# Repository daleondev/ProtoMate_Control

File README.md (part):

# ProtoMate Control

Control software running on the robot controller of the ProtoMate SCARA Robot.

## Current target: Arduino GIGA R1 WiFi

**M4 runs `io::Application`; M7 runs `ui::Application`.** Each independently
linked image owns its main, ThreadX kernel, C++ runtime, heap, TLS, threads,
message bus, coroutine context and ICC bridge. Common implementations are
compiled separately for each core. ICC uses bounded shared-SRAM queues with
urgent, normal and background lanes; M7 writes the physical USB-C CDC console.

The STM32H747 CubeMX, HAL, external-flash bootstrap and build port are implemented.
**Both applications boot from QSPI; USB/ICC services and STEP generation under combined load are verified.**
Factory backups are preserved. [Wiring, memory, backup/flash/debug commands and acceptance gates](#arduino-giga-hardware-boot-and-bring-up)
are documented below. Linux keeps the paired in-process transport for tests.

M4 exposes STEP/DIR/enable, switches, DM542T/TMC2209 drivers, feedback and the
future EtherCAT SPI connection. M7 owns the RGB LED, user button, display/touch
and console. M7 mounts persistent internal-flash storage at `/flash`; M4 does
not mount the volume. Both runtimes include filesystem support.
Motor construction leaves all drivers disabled; initialization, enabling and
motion are explicit CLI operations. Display/touch bring-up uses `display`
commands. The shared TouchGFX robot HMI opens Home on M7 and Linux, using the same
motion client and job history as the CLI. See the [HMI guide](docs/gui/hmi/README.md).

## Remote-control integration and future supervision

OPC UA is integrated as a third UI frontend alongside GUI and CLI. The LAN9255
supervisor remains future work. This hobby project makes no certification or
SIL/PL claims. Powered robot commissioning remains separate from software and
motor-disconnected electrical tests.

### OPC UA interface on M7 using open62541

**Remote-motion endurance is not yet qualified:** intermittent network/server latency
can exceed the unchanged 500 ms control-source deadline. Read-only monitoring and
short electrical workflows pass; normal firmware starts with remote permission OFF.
See the measured blocker in the qualification report linked below.

The server uses the existing motion client, planner, source-aware execution jobs
and M4 admission. Its explicit reflection catalog publishes 187 application nodes
(68 methods), with stable string NodeIds and bounded typed records. The namespace
is `urn:protomate:control`; default subscriptions publish at 100 ms (50 ms minimum).
No network read requests fresh IO work.

- `src/ui/opcua` (`proto::ui::opcua`) owns the catalog, server, NetX/POSIX ports and
  allocator. `platform/network` owns Wi-Fi/SDIO/NetX. M4 links neither stack.
- GUI and OPC UA share `ui::Services`; CLI retains the same application-owned
  motion client and job history. Existing ownership, units, planning and stop
  semantics apply to all frontends.
- Remote commands require local permission, **OFF on every boot**. Anonymous
  SecurityPolicy None is intended for the trusted LAN. The client worker checks
  500 ms remote expiry independently of networking/rendering, using 100 ms
  heartbeats and explicit held-jog supervision. Disconnect never replays motion.
- Settings → Network and USB `network setup` provide local setup. One Wi-Fi
  profile is saved on internal flash; passwords are not exposed remotely or logged.
  Linux uses OS networking. `opcua status|start|stop|restart` and
  `opcua remote on|off` expose local management.
- Dedicated SDRAM reservations provide 512 KiB for OPC UA, 256 KiB for networking
  and 128 KiB for presentation snapshots/USB byte rings, preserving active
  framebuffers, M4 memory and ICC SRAM4. Another 128 KiB remains unassigned.
  The server's internal stack is 14 KiB, based on measured complete-catalog use.

See the [integration guide](docs/opcua/README.md),
[generated node reference](docs/opcua/nodes.md),
[architecture and memory diagrams](docs/opcua/architecture.md), and
[measured qualification status](docs/opcua/verification.md).
The [standalone Wi-Fi sample](examples/opcua_sample/README.md) remains buildable.

### LAN9255 SAM E53 supervisor with FSoE

Explore using the integrated SAM E53 as a dedicated supervisor and EtherCAT
gateway, including an FSoE endpoint for a remote FSoE controller. This would
replace the erased-SAM/direct-GIGA-to-ESC arrangement for this future variant:

```text
EtherCAT + FSoE -> LAN9255 ESC -> SAM E53 -> separate SPI -> GIGA M4
                                  |
                                  +-> independent motor shutdown hardware
```

- Restore SAM firmware and move EtherCAT slave application ownership there.
  Process FSoE locally; forward ordinary command/status data to M4 through a
  bounded SPI protocol. FSoE requires a corresponding remote FSoE main instance;
  an ordinary EtherCAT master alone does not supply that logic.
- Investigate the separate SPI exposed at mikroBUS J18 for the GIGA link.
  J3 taps the ESC bus and must not be driven by two independent masters. The
  current documented J3 wiring stays unchanged until this variant is implemented.
- Give the supervisor physical authority to withdraw motion permission without
  GIGA cooperation. A GIGA enable request may only enable motion while the
  supervisor, watchdog and local protective inputs also permit it.
- Default to inhibited operation during reset, power loss or watchdog expiry;
  latch trips and require deliberate recovery. Include an external watchdog
  driven by completed supervision cycles, not an autonomous timer heartbeat.
- Evaluate independent driver-enable inhibition and monitored switching of the
  motor-power branch while keeping controller power available. Select the output
  topology after checking failure behavior, stored energy and regeneration.
  DM542T/TMC2209 enable inputs are ordinary controls, not documented STO inputs;
  account for the existing interface polarity rather than simply disconnecting
  an enable wire. A stop message to M4 alone cannot provide this authority.
- Determine whether Axis 3 needs a brake or other load-retention mechanism before
  removing holding torque. Controlled deceleration through M4 is useful, but
  independent shutdown must still work if M4 fails.
- Verify with motors disconnected first: GIGA/SAM stalls and resets, lost/stale
  FSoE and SPI traffic, broken supervision, shutdown-output faults and prevention
  of unintended restart. Later validate actual stopping and load retention.

FSoE protects communication integrity; it does not by itself make the SAM,
outputs or mechanics fault tolerant. The intended outcome is a tested hobby
supervisor with independent shutdown, without a certification program.
References: [EVB schematic, page 22](docs/ethercat/EVB-LAN9255-Evaluation-Board-Users-Guide-50003106.pdf)
and [ETG FSoE overview](https://www.ethercat.org/safety/).

## Motion API: motors, axes and robot

M7 owns the motion client, bounded job history, axis conversion and robot planning.
M4 owns admission, driver state, execution and local stopping. CLI commands are
asynchronous: a returned job ID means submitted; `motion jobs <id>` reports IO
acceptance and the eventual result. Returning to the prompt does not cancel a move.

| Control | Units | Commands |
|---|---|---|
| `motor` | Shaft degrees / rpm | Existing raw moves, homing, dynamics and buffering |
| `axis` | Axis 1/2 degrees; Axis 3 mm | `status`, `move`, `moveto`, `home`, `jog`, `stop` |
| `robot` | Joint coordinates or Cartesian mm | `status`, `home`, `move joints`, `moveto joints`, `move point`, `moveto point`, `stop` |
| `motion` | Shared lifecycle/jobs | `init`, `enable`, `disable`, `status`, `jobs`, `wait`, `cancel`, `stop`, `abort` |

`motion init` leaves drivers disabled. Initialize and enable explicitly, then home
before absolute/axis/robot motion. Execution requires the native simulator's
mechanical configuration or a verified physical configuration. The physical
configuration is deliberately unset. Preview fixtures are never substituted for it.

Examples after homing:

```text
axis move shoulder -5 --speed 10
axis jog z -1 --duration 1
robot moveto joints 30 -30 10 --speed 0.25
robot move point -1 -1 0
motion jobs
motion wait 4 --timeout 10
motion cancel 4
```

Axis dynamics are deg/s, deg/s², deg/s³ or mm/s, mm/s², mm/s³. Zero/omitted values
select configured defaults. Robot `--speed`, `--accel`, `--decel` and `--jerk` are
factors of configured limits in (0,1]; zero selects defaults. Speed defaults to
0.25. Cartesian point moves interpolate **joints**, so their TCP paths can curve.
Straight Cartesian paths remain previews; blending, live override and hold/resume
are not exposed as executable robot features.

M4 atomically excludes command families. Raw motor commands can coexist under
existing per-motor buffering rules; axis jobs may run on separate axes; a robot
job reserves all three. Families cannot mix. Reservations start before executable
planning and last through deceleration and cleanup. Busy results identify the
owner. Configuration/state revisions are checked again before starting; stale
plans emit no pulses. Read-only status and previews remain available.

`motion jobs` retains 32 execution records. Waiting explicitly does not transfer
ownership; a wait timeout leaves the motion running. `axis stop` also stops the
whole group if that axis belongs to a robot job. Axis/robot stops decelerate with
holding torque retained. Raw `motor stop` remains an immediate abort; abort and
disable invalidate affected references. No stop or reconnect resumes motion.

The configured ceiling is **6,250 pulses/s on each axis**, with microsteps
**16 / 16 / 8**. Joint/point moves share one normalized profile and one scaled
stopping-progress profile. Endpoints are quantized once, and completely zero
moves do not arm outputs. Finite programs, including stopping continuations, are
limited to **90 seconds**. Continuous jog uses rolling timing toward the actual
soft-limit boundary; the default timed jog requests deceleration after one second.

Two deadlines serve different purposes: the UI ownership lease is **250 ms**,
renewed in one batch every **50 ms**; local M4 execution maintenance uses a
**40 ms** renewal and **80 ms** committed frontier. The execution worker still
services refills and stops every millisecond; its local keepalive remains 40 ms.
UI loss selects an already
installed brake on M4. An M4 execution failure invokes the hardware guard and
invalidates uncertain references; it is not a guaranteed controlled stop.

The Linux workflow exercises the native simulated plant through the production
CLI, ICC and controller. Brake construction preserves the incoming state and
accepts only binary64 roundoff at acceleration limits (eight machine epsilons,
relative to the limit). Exact captured-input, phase-boundary, scaling and
out-of-limit regressions cover this numerical boundary.

The current motion review has separate software and electrical results. Short
motor-disconnected analyzer captures pass for raw commands (**18/18/9 pulses**),
coordinated completion (**400 per axis**) and controlled stopping (**266 per axis**).
HIGH time is 120–121 samples at 24 MHz; coordinated rising-edge skew is at most
one sample. Physical ENABLE remains inactive throughout. These captures peak
near 711 pulses/s and do **not** qualify the configured 6,250-pulse/s ceiling.

The concurrent jog/independent-axis ICC failure is fixed. The M4 urgent sender
was exhausting the heap when allocating a 4,228-byte temporary coroutine for
another outgoing frame; UI then reported the missing heartbeat. Each sender now
reuses one persistent frame allocated at startup. A host allocation regression
and repeated application-level overlaps verify the fix. Heartbeat, ownership
and motion deadlines are unchanged. See the [current review](docs/motion-current-state/review.md)
for firmware identities, capture results and the remaining physical qualification.

The review fixes an overall homing deadline, missing preparation-version
validation, an interrupted-wait wakeup race, telemetry waiting on raw startup's
command lock, a native display-mutex preemption deadlock, and an unnecessary
peak allocation when STEP scratch storage grows. Preparation/start failures now
retain their stage and allocation failures report capacity exhaustion. The
native simulator caches mechanical configuration before starting live transport.
Its clock waits for interrupt-woken controller work to suspend before advancing
the next event, and simulated display refresh uses that same clock. This prevents
instrumentation overhead from starving homing behind repeated periodic wakeups.

The ordinary interaction objective remains approximately **200 ms to start
changing motion**, not to reach rest. The current captures establish pulse
behavior, not a worst-case admission/stop-onset bound or maximum-rate endurance.
The complete native motion workflows pass with ASan/UBSan, including
homing → stop → homing and checks for unwanted seek pulses after switch contact.
This functional simulation does not qualify hardware scheduling or timing.
Clang-tidy is clean across all 430 production compilation contexts (Linux, M4
and M7), with no parse blockers; unit tests remain excluded.
See the [current review](docs/motion-current-state/review.md) for exact
build, test, firmware and capture evidence.

Powered mechanical acceptance requires calibrated limits and transmissions.
[Executor architecture and verification](src/io/motion/EXECUTOR.md).

## Native Linux robot simulation

Build as usual, then launch **`build/debug-linux/Application`**. This one
executable forks into a native simulation process and a controller process,
opening the TouchGFX window plus a separate robot window. Use
`--headless` to omit only the robot window. See [simulator usage and model
boundaries](src/simulation/README.md) for the provisional physical profile,
fault controls, persistent media, signal capture and verification commands.

The robot window displays native simulated shaft/axis state, not motion requests
or controller position estimates. The controller retains the production IO
state machines, drivers, STEP generator, FileX/LevelX and UI/IO ICC. Emulated
motion hardware and physical state live in the separate native process.

## Platform layout

| Directory | Responsibility |
| --- | --- |
| `platform/boot/` | Board startup, recovery images, memory protection and GIGA flash partition layout |
| `platform/hal/` | Hardware contracts, drivers, devices, board wiring and core selection; includes the inter-core lane contract |
| `platform/simulation/` | Linux simulator wire contract, shared memory, HAL mailbox and interrupt handoff |
| `platform/runtime/` | ThreadX integration, C/C++ runtime and filesystem/storage implementations |

The GIGA partition header is shared by boot MPU setup and the runtime flash
adapter; the partition addresses and erase geometry are defined in one place.

## Application layout

| Directory | Responsibility |
| --- | --- |
| `src/common/` | Shared contracts, motion profiles, application lifecycle concept, ICC bridge and transports |
| `src/io/` | M4 entry point, IO application, motor ownership and motion execution |
| `src/simulation/` | Native hardware process, machine models, independent SDL/OpenGL viewer and tests |
| `src/ui/` | M7 entry point, UI application, CLI, shared GUI, axis conversion and robot planning |

Each firmware compiles only its own application target, `proto::io` or
`proto::ui`. Both use `proto::common`. These are compiled static libraries;
their nested `INTERFACE` targets collect sources privately into the owning
library. Tests and examples link the compiled libraries so implementation files
are compiled once per build. Public include paths start at `src/`, for example
`common/icc/bridge/Bridge.hpp` and `io/app/Application.hpp`. The Linux entry point in
`src/main.cpp` retains the in-process paired transport for host development and
lifecycle tests. It is not compiled into either GIGA image.

The [application concept](src/common/app/Application.hpp) enforces `void start()`,
`void requestStop()` and `void join()` without inheritance. Construction initializes
logging; application workers launch in `start()`. `start()` is one-shot;
`requestStop()` is an idempotent thread-safe notification; `join()` waits for
completion. Destruction requests a stop and joins. Call start/join/destruction
from the lifecycle owner, outside workers.

`runtime::thread::Definition` annotations in each `app/Application.hpp` declare
its threads; `app/Application.cpp` defines their entries.
[ThreadGroup](platform/runtime/ThreadGroup.hpp) creates all workers before
releasing them. The ICC worker runs the context; the application worker waits
for a stop request, then drains the bridge before stopping its context. Peer
shutdown or link failure wakes the application worker. Each application requires
a transport; the bridge is a concrete member with no optional execution path.

Each application exposes a lifecycle `state()`: `Starting`, `Ready`, `Stopping`,
`Stopped` or `Fault` ([shared definition](src/common/app/State.hpp)). IO publishes
its state on the latest-only `io/controller/state` topic every 100 ms. UI owns
[`SystemState`](src/ui/app/SystemState.hpp), combining its local state, the
received IO state and ICC connection health; `ui::Application::systemState()`
returns this snapshot. Refresh uses timers on the existing ICC workers.
The CLI command `state` displays the same combined state and LED colour, both
controller states, and whether the received IO state is fresh. `help state`
describes the command; reading state does not issue an IO request or move motors.

UI displays the combined state on the GIGA's onboard RGB LED:

| Colour | Meaning |
| --- | --- |
| Green | Both applications are `Ready`, ICC is connected and IO state is fresh |
| Yellow (red + green) | Starting, awaiting IO state, or orderly stopping/stopped |
| Red | Application fault, ICC failure, or no IO state for 500 ms while connected |

Blue stays off. Freshness uses UI's receive clock; timestamps need not be
synchronized between cores. Fault indications latch until application restart;
shutdown cannot clear them. Final topic delivery is best effort, with ICC's
orderly goodbye distinguishing normal peer shutdown from communication failure.
These are **controller application states**, not motor readiness or enable
indicators. Green does not mean drivers are initialized, motors are referenced,
or motion is enabled. Motor telemetry and admission checks remain separate;
an LED or lost communication cannot confirm that physical motion has stopped.
GIGA Debug verification checks the LED GPIO levels: green during normal paired
operation, yellow after CLI shutdown, and red after halting M4 until a coordinated
restart. Shared motor enable remains inactive throughout these checks.

[`io::motion::Controller`](src/io/motion/Controller.hpp) owns three `StepperMotor`
instances, their shared STEP generator and enable output. Drivers and feedback
belong to each motor. `initializeDrivers()` configures the drivers and starts the
idle timebase; `enable()` verifies readiness before energizing the motors.
Controller move/reference methods preserve independent axis execution and
buffering. `stop(id)` stops one motor, `stop()` stops all while retaining torque,
and `disable()` also removes enable and invalidates references. Driver faults
immediately drop shared enable; a diagnostic worker cancels and joins all motion.
Recovery requires explicit initialization and enabling. IO shutdown disables the
motors before draining ICC. Motor settings live in `io/app/Application.cpp`:
1.8° full steps, 16/16/8 microsteps for M1/M2/M3 and placeholder 135° shaft
reference coordinates. These shaft placeholders do not supply a calibrated axis
or robot configuration.

The motor service dispatcher handles urgent stop/disable requests and telemetry.
One bounded command worker (priority 2, 16 KiB ARM stack) executes ordinary services and program preparation;
additional ordinary requests return `Busy` while it is occupied. UART verification
and initialization run outside the controller admission lock, and enable settling
is cancellable. Stop invalidates pending initialization/enable work and queued
ordinary requests; only a new explicit command can enable the motors afterwards.
Velocity updates enqueue under the admission lock and wait outside it.

`src/ui/cli/` contains the annotation-based parser, filesystem and utility
commands, Linux terminal frontend and direct motor commands. Registration uses
`ui::cli::register_commands` with a parser owned by the CLI thread. Each command
module has its own per-parser `std::call_once` guard. Motor callbacks use the
application-owned `ui::motion::Client`; only IO owns the physical controller.

M7 exposes the CLI through **USB-C CDC** (no UART bridge). Use `help` or
`help <command>`. Available commands are `pwd`, `cd`, `ls`, `touch`, `mkdir`,
`rmdir`, `rm`, `cp`, `mv`, `cat`, `echo`, `grep`, `time`, `stack`, `heap`, `state`,
`display`, `motor`, `motion`, `axis` and `robot`.
Quoting, wildcard expansion, pipes and `>`/`>>` redirection are supported.
For example, `echo "hello world" | grep world` and `time "heap io"`.
`heap ui` / `stack ui` inspect UI locally; `heap io` / `stack io` request IO's
memory diagnostics through the `io/memory` ICC service. The controller argument
is required. `time` measures execution on UI, including any remote round-trip wait.
Filesystem commands use the host filesystem on Linux and FileX on M7.
On GIGA, `/flash` is persistent internal-flash storage; see
[persistent files](#persistent-files-in-internal-flash) for capacity and behavior.

Motor commands use **motor-shaft degrees and rpm for all three motors**, including
M3. `motor` prints a guide; `help motor move` lists annotated options.

```text
motor driver init
motor enable
motor move m1 -90 --speed 5
motor jobs
motor status m1
motor stop m1
motor disable
```

- `motor status [m1|m2|m3|all]` shows commanded position/velocity, feedback and reference state.
- `motor driver status [motor|all]` shows driver readiness, alarms and latched faults.
- `motor driver init` initializes/recover drivers and the STEP timebase while disabled.
- `motor enable` / `motor disable` operate the shared enable; disabling stops work and invalidates references.
- `motor move <motor> <degrees> --speed <rpm>` submits a relative move.
- `motor moveto <motor> <degrees> --speed <rpm>` requires successful homing.
- `motor home <motor> [--seek 5] [--latch 0.5] [--timeout 30]` seeks, releases, slowly re-latches and finally releases the switch again, retaining the coordinate established at the latch.
- `motor speed <motor> <rpm>` replans the uncommitted remainder of an active move. It can be rejected once all remaining pulses are already scheduled.
- `motor defaults <motor> [--accel <deg/s²>] [--decel <deg/s²>] [--jerk <deg/s³>]` reads/updates idle motor defaults in RAM.
- `motor stop [motor|all]` aborts the selected motor and its buffered successor while retaining holding torque and invalidating its reference. Other independent motors continue; targeting a current robot group aborts that whole group.
- `motor jobs [id]` uses the shared execution-job registry. `motion jobs [id]` shows all command families; returning from a CLI command does not cancel its job.

Moves accept `--accel`, `--decel`, `--jerk` (zero selects the motor default),
`--timeout` (seconds, zero means unlimited) and `--buffer` (`aborting`, `buffered`,
`blending-low`, `blending-previous`, `blending-next`, `blending-high`). A motor can
have one queued successor. A configured default jerk of zero selects a trapezoid.
`accepted` includes queued/executing work; only a terminal result confirms its outcome.
INDEX feedback is labelled as a pseudo measurement of driver phase.
Axis conversion and coordinated positioning are exposed through `axis` and `robot`,
with the family exclusion and configuration requirements described above.

Linux uses ncursesw with separate logs, line editing and command history when
attached to a terminal. Redirected input/output, `TERM=dumb`, or
`SIMPLCITY_CLI_PLAIN=1` select the plain frontend. Console EOF, Ctrl-C, or Ctrl-D
on an empty interactive line shuts down the application pair. Application or
peer shutdown also interrupts an idle CLI. Plain/serial lines are limited to
4096 bytes; oversized lines are rejected. M7 receives bytes into a bounded IRQ
buffer while commands execute; input errors stop the console instead of
executing truncated input. The serial frontend echoes input, so disable local
echo in the PC terminal.

The shared message catalogs live in `src/common/icc/catalog/`:

- [topics.hpp](src/common/icc/catalog/topics.hpp): `Topics`, with `TopicPublisher` annotations.
- [services.hpp](src/common/icc/catalog/services.hpp): `Services`, with `ServiceProvider` annotations.
- [actions.hpp](src/common/icc/catalog/actions.hpp): `Actions`, with `ActionProvider` annotations.

Both applications register all three catalogs in their constructors using their
own IO/UI role. `Topics::io_logs` carries IO log text to UI. `Topics::io_motor_state`
publishes all three motor states at up to 20 Hz, including while idle or disabled.
Both the bridge and UI subscription use latest-only delivery. `Services::io_memory`
provides memory diagnostics. `Services::io_motor` carries initialization,
enable, speed and default-setting requests. `Services::io_motor_stop` reserves
urgent transport capacity for stop/disable. `Actions::io_motor_motion` carries
raw individual moves and homing, with periodic feedback and terminal results.
`Services::io_trajectory` handles authoritative snapshots, reservations and bounded
program preparation. `Services::io_trajectory_control` uses the urgent lane for
batched lease renewal, stop, abort and reservation release. `Actions::io_motion`
starts a prepared axis/robot program and retains its lifecycle through cleanup.
Shared motor payloads live in `src/common/motion/Motor.hpp`; compact versioned
program packets live in `src/common/motion/Trajectory.hpp`. Both use the existing
ICC bridge rather than a separate motion transport.

`motor status` and `motor driver status` read UI's latest snapshot without a
service request. Missing telemetry, disconnection and samples older than 500 ms
produce explicit errors. Freshness uses UI's local receive clock; the snapshot's
IO timestamp is informational, and its increasing sequence rejects duplicate or
out-of-order samples. The worker waits 50 ms after publishing; blocking IO or ICC
processing can extend the interval. It does not catch up missed publications in
a tight loop that would starve diagnostics and logging. Command replies contain the outcome, `commandGeneration`
and operation-specific values (motion defaults or the scheduled speed-change
pulse), without copying motor states. Actions still report acceptance and terminal
results independently of telemetry.

IO's application worker drives `io::motion::Server`; blocking driver operations
and joins stay outside the ICC context. Controller completion callbacks only
wake this worker. UI's application worker caches telemetry and dispatches action callbacks for
`ui::motion::Client`, retaining its job handles until completion. Services and
action admission time out after three seconds; execution uses the requested
motion timeout. Lease renewals have a shorter 150 ms service timeout and only
one renewal request may be outstanding. No request is automatically retried. `commandGeneration`
rejects submissions overtaken by a stop, disable or initialization. Acknowledgements
update UI's generation immediately, so subsequent moves do not wait for telemetry;
older snapshots cannot roll it back. IO validates admission against its current
state rather than trusting UI's cache. Link shutdown
drains IO motion and disables the shared enable before closing its bridge. UI
reports uncertain communication outcomes as unknown rather than claiming a stop.

Diagnostic snapshots and collection live in `src/common/diagnostics/`. IO's
`io::diagnostics::Server` collects them on a dedicated worker; the CLI formats
both local and remote results using the same tables. Remote requests have a
two-second timeout, participate in UI shutdown cancellation and never fall back
to UI measurements on failure. At most two requests are outstanding at the IO
provider. Each response fits one ICC frame and includes up to 32 thread records
with names limited to 31 characters; omitted threads and shortened names are
identified in the output. Stack usage is sampled/saved usage and a recorded
high-water mark, not a continuous measurement. The collection copies thread
records under the local ThreadX interrupt lock, without allocation or formatting.
On Linux both controllers share the process allocator and ThreadX kernel; the
output explicitly labels that scope even when the request travels through ICC.

`reset all` immediately aborts motion and resets the complete GIGA, including both
controllers. STEP/enable outputs are inhibited before reset; startup leaves motors
disabled and references must be established again. During reset itself, GPIOs are
inputs: external STEP pull-downs and the disable-state enable bias remain required.
USB CDC disconnects during
reboot. This is **not** a controlled stop: use `motion stop` first when deceleration
is required. Individual `reset ui` / `reset io` requests are rejected without any
reset. ST does not guarantee CPU-only watchdog reset (RM0399 §9.7.36), and our ICC
transport currently requires coordinated startup. Linux reports hardware reset as
unsupported; close and restart the simulation instead.

IO's Pneumo sink publishes already formatted records on `io/logs`; UI adds an
`[IO]` prefix and writes them directly to the console without logging them again.
Original timestamps and levels remain intact. Each record is limited to 384 bytes
(longer records end with `[truncated]`), and both the outgoing bridge subscription
and UI subscriber retain the newest 16 records. Overflow counters are available
through bridge/subscriber statistics; the sink separately counts truncations.
Console output runs on a notification-driven UI worker, never in ICC callbacks.
On Linux it uses the console broker, including buffering before ncurses starts.

UI installs its own Pneumo sink for all levels before its first startup log.
It prefixes local records with `[UI]` and calls `cli::writeLog`, the same output
function used by the IO subscriber. Received IO records retain `[IO]` and bypass
the local sink. The CLI frontend does not replace either logging route.

The M4 entrypoint installs this sink as Pneumo's default for all levels. The motion
controller also passes it explicitly to its motors, so Linux's IO logs use the same
ICC path while UI retains its separate console routing in the shared process.
Shutdown closes the IO sink before stopping ICC and wakes/joins UI's log worker.
Logs are best effort and may be discarded at shutdown. These bounds apply to the
ICC path; Pneumo's existing asynchronous logger queue is separate. Logging remains
a thread-context operation, not an ISR-safe or allocation-free API.

| Thread in each GIGA image | ThreadX priority (lower is higher) | Stack |
| --- | --- | --- |
| ThreadX timer worker | 0 | Port default |
| `io.iccThread` | 4 | 20 KiB (32 KiB on Linux) |
| `intercore.notify` | 3 | 2 KiB (8 KiB on Linux) |
| `ui.iccThread` | 4 | 32 KiB |
| `ui.cliThread` | 5 | 16 KiB (64 KiB on Linux) |
| M4 motion executor | 1 | 8 KiB (16 KiB on Linux) |
| M4 command/preparation worker | 2 | 28 KiB (24 KiB on Linux) |
| M4 raw motion/homing worker (up to three) | 16 | 10 KiB (16 KiB on Linux) |
| `io.applicationThread` | 3 | 16 KiB |
| `ui.applicationThread` | 6 | 16 KiB |
| Runtime main/application entry | 15 | 8 KiB |
| M4 motion diagnostics | 18 | 6 KiB (8 KiB on Linux) |
| `io.diagnosticThread` (heap/stack service) | 20 | 4 KiB (16 KiB on Linux) |
| `ui.logThread` | 20 | 8 KiB |
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
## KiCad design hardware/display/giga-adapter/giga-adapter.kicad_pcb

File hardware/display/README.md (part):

# Smartwin–GIGA display adapters

**Local electrical, manufacturing and recorded visual checks pass.**
Both use complete outer-layer routing, two continuous inner GND planes and
stitched outer fills. Authorized placement changes put GIGA R33–R48 beside J8
and reposition display C9/TP8 and R16/R17 for direct supply and supervisor connections.
Connector positions and board mechanics remain fixed.
See [current validation status](manufacturing/layout-unification-status.json).
The matching releases below are ready for upload and AISLER processing review.

**Component selection:** the working KiCad schematics and PCBs now contain the
approved [purchasing selections](procurement/README.md), including their actual
manufacturer, MPN and voltage ratings. This is a component-metadata update;
copper, footprints, placement and silkscreen are unchanged. The frozen release
archives below retain their original component metadata. Use the working projects
and current procurement list for assembly; this update does not constitute a new
fabrication release or renew the archives' source-hash inspection records.

The **four-layer display adapter (revision G)** and **four-layer GIGA adapter
(revision F)** connect the Smartwin **SMMH0701024600S-C20** to the Arduino
**GIGA R1 WiFi**, preserving the firmware's display pin assignments.
Open either project in KiCad 10; both use `libraries/` and require no downloaded
symbol or footprint library. Keep this directory structure when moving them.

Release files:

- [Display G: AISLER ODB++ upload](releases/display-adapter-rev-G-aisler-odb.zip)
- [GIGA F: AISLER ODB++ upload](releases/giga-adapter-rev-F-aisler-odb.zip)
- [Display G: review and soldering package](releases/display-adapter-rev-G-aisler-review.zip)
- [GIGA F: review and soldering package](releases/giga-adapter-rev-F-aisler-review.zip)
- [Source bundle G: projects, libraries, models and tools](releases/smartwin-giga-rev-G-source.zip)
- [Nominal GIGA mating assembly](assembly/giga-mated-rev-F.png)
- [Component lists and Mouser procurement](procurement/README.md): quantities for one
  board pair, explicit substitutes, stock evidence and remaining sourcing gaps;
  the DC jack is already owned.

Upload only the two ZIPs labelled **AISLER ODB++ upload**, one job per board.
The review packages contain fabrication references, procurement BOMs, placement
and soldering drawings. They are not assembly orders. `releases/SHA256SUMS`
identifies the exact archives.

| Project | Board | AISLER profile | Finish |
|---|---|---|---|
| `display-adapter/display-adapter.kicad_pro` | Rev G, 4 layers, 55 × 50 × 1.6 mm | `aisler-4-layer-hd-drc` | ENIG |
| `giga-adapter/giga-adapter.kicad_pro` | Rev F, 4 layers, 111 × 53.34 × 1.6 mm maximum | `aisler-4-layer-hd-drc` | ENIG |

Both are **bare boards**, with 35 µm copper on every layer, green solder mask
and white silkscreen. All components are sourced and installed separately.
**AISLER processing acceptance is pending** until the exact upload previews,
options, bridges and netlist notes have been inspected. Physical qualification
also remains pending; local verification does not establish either acceptance.
The [electrical and fabrication review](manufacturing/REVIEW.md) records the
current release limits. These are prototype fabrication packages; full RGB
timing and dynamic supply qualification are still open.

The display adapter carries a **DF23C-50DP-0.5V(92) plug on its underside**.
It mates with the existing display connector; do not remove the display connector
or solder the adapter directly to the display flex. The GIGA adapter plugs into
the existing headers, with stacking sockets preserving access to every collected
contact. USB, SWD, buttons, LEDs and stacking contacts remain accessible. The inward power tab occupies the upper central area; the lower service opening remains clear.

**Physical operation has not been tested.** Fabrication verification and first-board
electrical qualification are separate. The machine-readable release status and
verification reports in `manufacturing/` identify which checks have passed.
Do not manufacture a working-directory draft without its matching release ZIP.

## Connection and power

```text
24 V -> shield J10 -> fuse / TVS / TPS26600
                        |                  |
                   TSR 1-24120       0.8 A ribbon fuse
                      12 V                 |
                   blocking D3          60-way FFC
                        |                  |
                     GIGA VIN       +------+------+
                                    |             |
                                TSR 2-2433    TSR 1-2450
                                3.3 V BKL        5 V
                                    |         TPS7A91
                                backlight    3.296 V logic
                                                  |
                                      TFT / touch / buffer reference
Both panel rails -> supervisors -> READY -> reset/standby/PWM gates + GIGA D70
```

Connect the existing **regulated 24 V supply to shield J10 with a centre-positive
5.5 × 2.1 mm barrel plug**. J10 uses the supplied `BarrelJack_Horizontal_AISLER`
DC-005 footprint: pin 1 = +24 V; pins 2 and 3 = GND (sleeve and sleeve switch;
plug detection is unused). Allow at least 2 A supply capacity for this assembly; the input
protection limits combined current to approximately 1.49 A. The recommended
supply range is 24 V ±10%. Keep grounds common with the robot. This input powers
both GIGA and the display; the display adapter has no separate power terminal.

- **Shield U8: TRACO TSR 1-24120**, 24 V to 12 V, rated 1 A output. D3 feeds
  VIN through a Schottky diode, so actual VIN is slightly below 12 V. VIN reaches
  both corresponding GIGA header contacts, J5.8 and J9.24.
- **Display U1: TRACO TSR 2-2433**, 3.3 V / 2 A, supplies only the backlight
  contacts 5–8. Four local 47 µF capacitors support its load. Keep total output
  capacitance, including the panel, below the module's 900 µF limit.
- **Display U2: TRACO TSR 1-2450**, 5 V / 1 A, feeds **U3 TPS7A9101DSKT**.
  The precision LDO supplies TFT pin 10, touch pin 49 and the interface-reference
  return. Its 31.2 kΩ / 10 kΩ, 0.1% divider sets **3.296 V**. The regulator's
  1% line/load/temperature accuracy gives much more room inside the panel's
  3.0–3.6 V range. The 47 nF soft-start capacitor sets an approximately 6 ms ramp;
  the component-limit estimate is 3.3–11.3 ms. Keep SS_CTRL grounded.
- The logic load allocation is **0.45 A**; the backlight contact ceiling is
  **1.2 A** total, subject to current sharing among its four 0.3 A contacts.
  Allow up to **0.75 A at GIGA VIN** in the combined input budget. These are design
  allocations, not measured panel maxima or simultaneous converter nameplate ratings.
- **USB-C may remain connected for CDC CLI/logging.** GIGA retains its onboard
  USB/VIN power arrangement. D3 blocks reverse feed from VIN into U8 when only
  USB is present. USB alone runs GIGA, but does not power the display or the
  external 24 V rail. Do not connect another source to VIN simultaneously.
- **GIGA_3V3 and PANEL_3V3 remain separate.** Three FFC contacts return the panel
  rail to the panel sides of the AXC/TCA interface devices. This return carries
  interface current, while the backlight's 3.3 V current stays on the display
  board. All grounds are common.

Shield F1 is a **Bourns SF-1206SA200M-2, 2 A/65 V time-lag fuse** and D1 a
bidirectional **SMBJ33CA** TVS. F1 uses Bourns' 1.45 × 1.80 mm pads with a
1.50 mm gap. At the 1.056 A input-load budget its typical cold resistance gives
0.148 V drop and 0.156 W dissipation; see the temperature/loading allowance in
[`power-budget.json`](manufacturing/verification/power-budget.json).
U7 **TPS26600PWPT** provides reverse-polarity/reverse-current protection,
undervoltage and overvoltage cutoff, controlled inrush and current limiting.
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
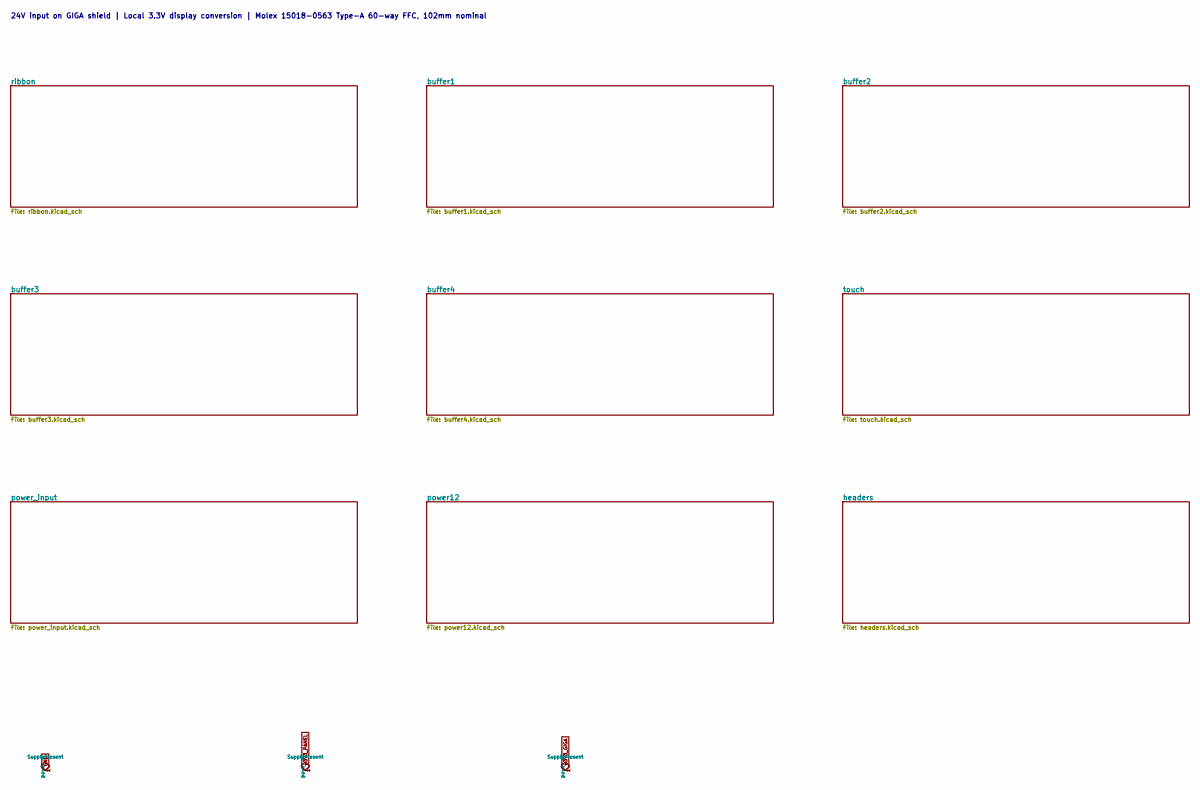
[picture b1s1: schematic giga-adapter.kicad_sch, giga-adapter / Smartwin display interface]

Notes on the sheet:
24V input on GIGA shield | Local 3.3V display conversion | Molex 15018-0563 Type-A 60-way FFC, 102mm nominal

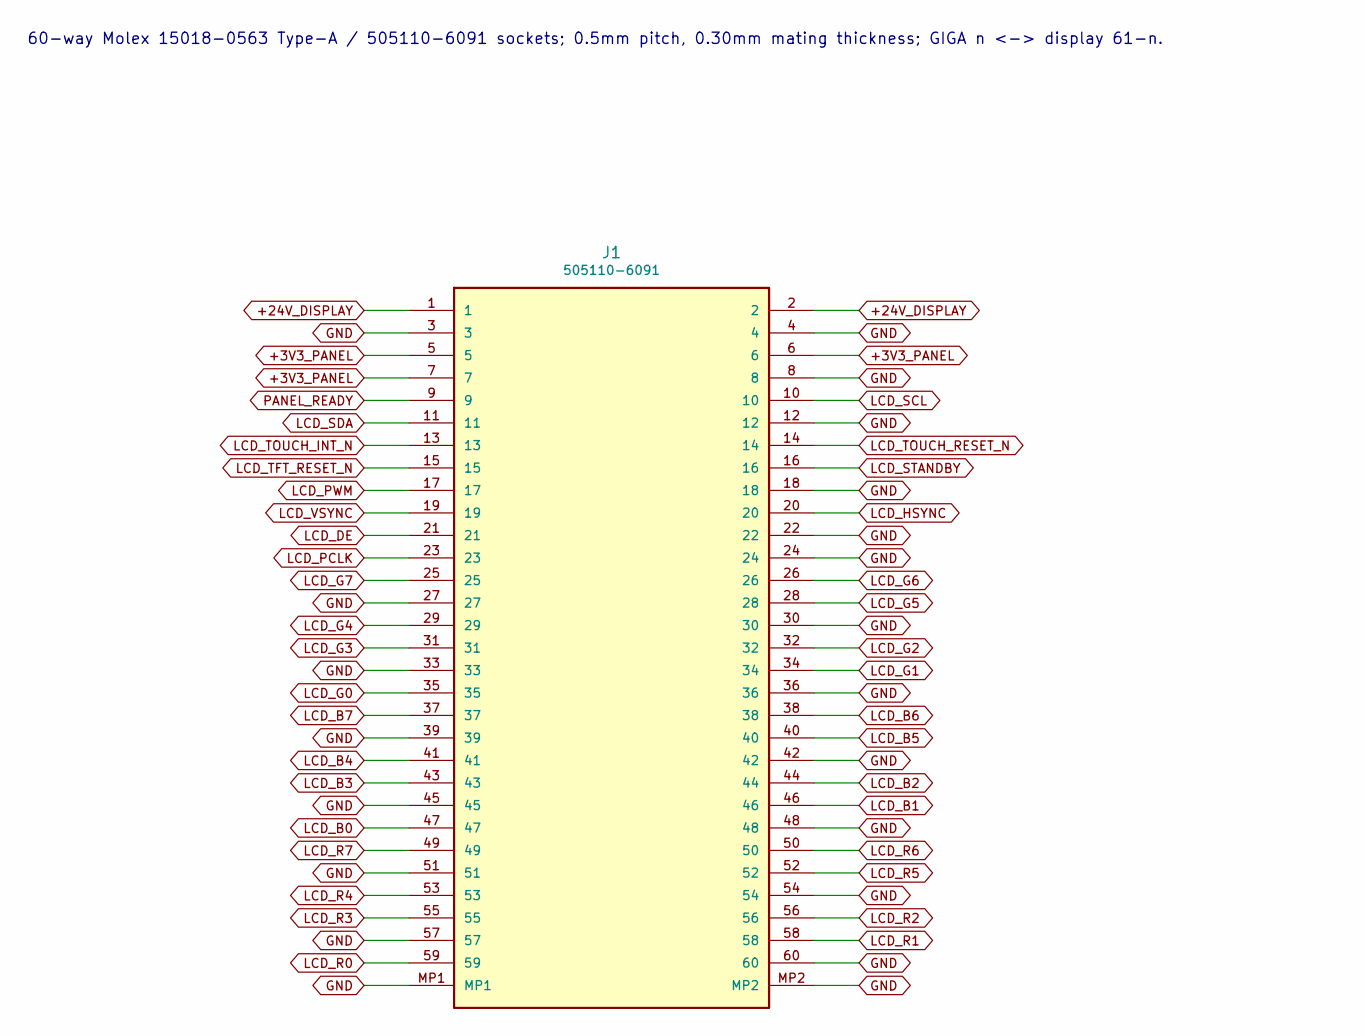
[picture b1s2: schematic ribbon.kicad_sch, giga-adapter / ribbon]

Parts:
J1: 505110-6091; Molex_505110-6091_1x60_P0.50mm; MPN 505110-6091

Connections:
+3V3_PANEL: J1.5, J1.6, J1.7; also elsewhere on the board
+24V_DISPLAY: J1.1, J1.2; also elsewhere on the board
GND: J1.3, J1.4, J1.8, J1.12, J1.18, J1.22, J1.24, J1.27, J1.30, J1.33, J1.36, J1.39, J1.42, J1.45, J1.48, J1.51, J1.54, J1.57, J1.60, J1.MP1, J1.MP2; also elsewhere on the board
LCD_B0: J1.47; also elsewhere on the board
LCD_B1: J1.46; also elsewhere on the board
LCD_B2: J1.44; also elsewhere on the board
LCD_B3: J1.43; also elsewhere on the board
LCD_B4: J1.41; also elsewhere on the board
LCD_B5: J1.40; also elsewhere on the board
LCD_B6: J1.38; also elsewhere on the board
LCD_B7: J1.37; also elsewhere on the board
LCD_DE: J1.21; also elsewhere on the board
LCD_G0: J1.35; also elsewhere on the board
LCD_G1: J1.34; also elsewhere on the board
LCD_G2: J1.32; also elsewhere on the board
LCD_G3: J1.31; also elsewhere on the board
LCD_G4: J1.29; also elsewhere on the board
LCD_G5: J1.28; also elsewhere on the board
LCD_G6: J1.26; also elsewhere on the board
LCD_G7: J1.25; also elsewhere on the board
LCD_HSYNC: J1.20; also elsewhere on the board
LCD_PCLK: J1.23; also elsewhere on the board
LCD_PWM: J1.17; also elsewhere on the board
LCD_R0: J1.59; also elsewhere on the board
LCD_R1: J1.58; also elsewhere on the board
LCD_R2: J1.56; also elsewhere on the board
LCD_R3: J1.55; also elsewhere on the board
LCD_R4: J1.53; also elsewhere on the board
LCD_R5: J1.52; also elsewhere on the board
LCD_R6: J1.50; also elsewhere on the board
LCD_R7: J1.49; also elsewhere on the board
LCD_SCL: J1.10; also elsewhere on the board
LCD_SDA: J1.11; also elsewhere on the board
LCD_STANDBY: J1.16; also elsewhere on the board
LCD_TFT_RESET_N: J1.15; also elsewhere on the board
LCD_TOUCH_INT_N: J1.13; also elsewhere on the board
LCD_TOUCH_RESET_N: J1.14; also elsewhere on the board
LCD_VSYNC: J1.19; also elsewhere on the board
PANEL_READY: J1.9; also elsewhere on the board

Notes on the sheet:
60-way Molex 15018-0563 Type-A / 505110-6091 sockets; 0.5mm pitch, 0.30mm mating thickness; GIGA n <-> display 61-n.

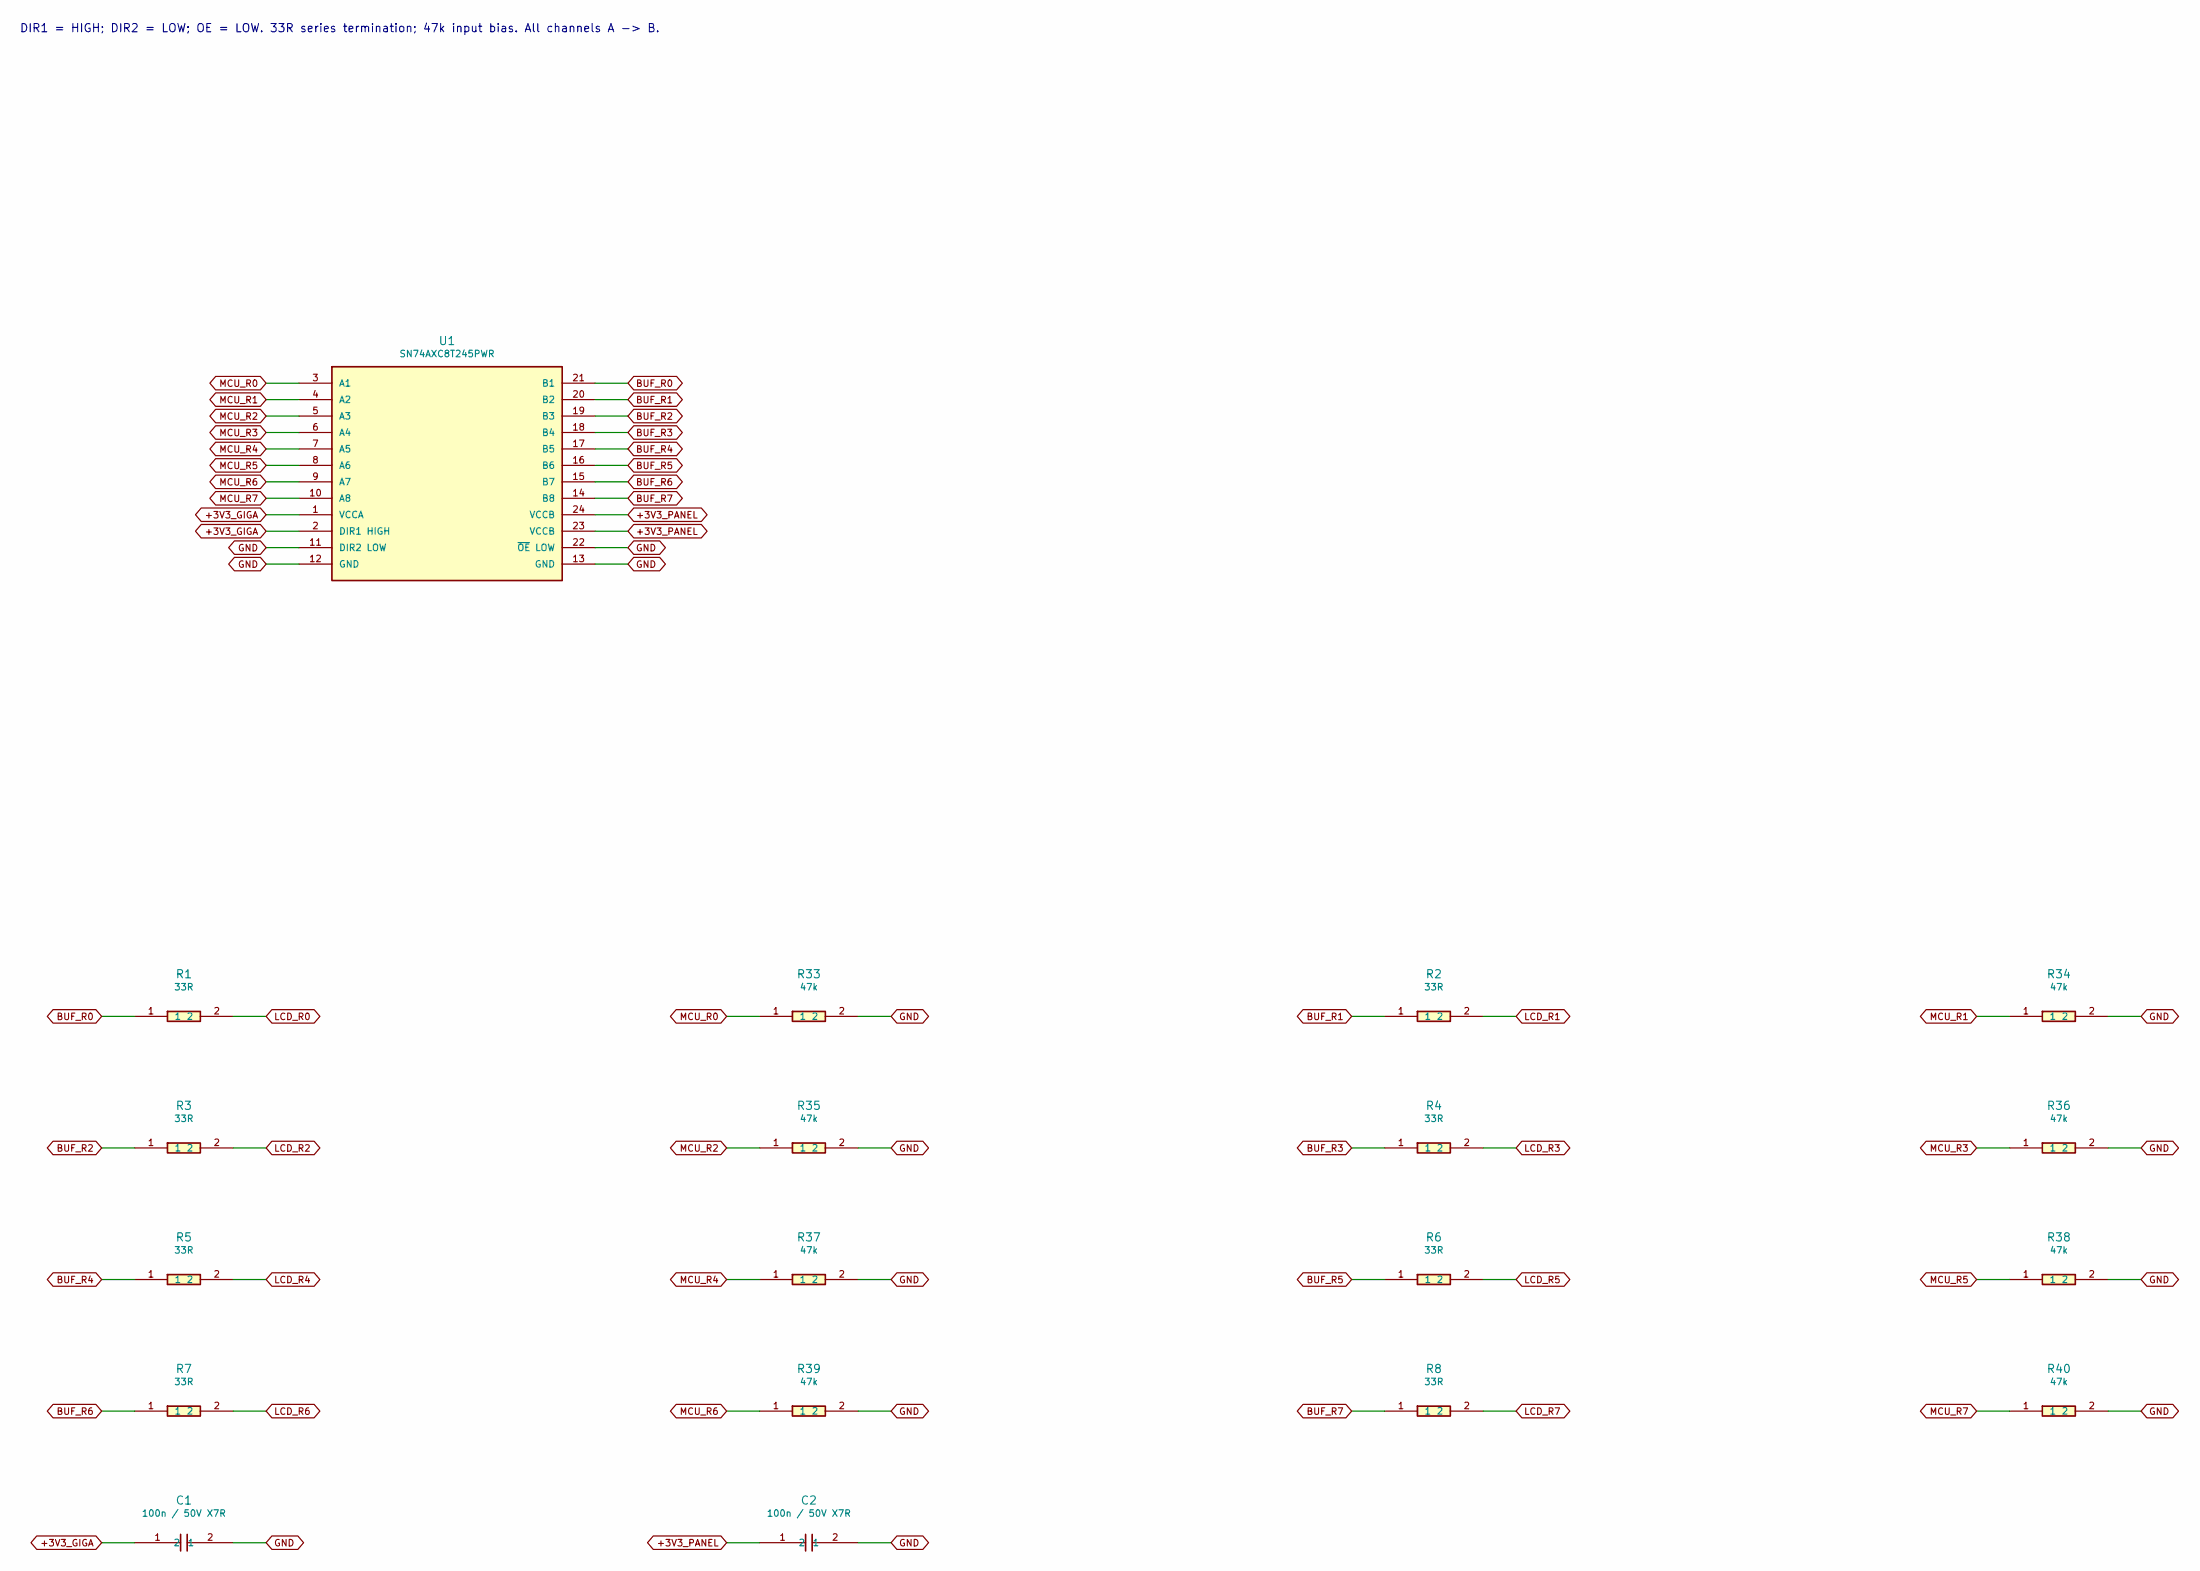
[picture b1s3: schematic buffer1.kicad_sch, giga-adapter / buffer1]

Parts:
C1, C2: 100n / 50V X7R; C_0603_1608Metric; MPN C0603C104K5RACTU
R1, R2, R3, R4, R5, R6, R7, R8: 33R; R_0402_1005Metric; MPN RC0402FR-0733RL
R33, R34, R35, R36, R37, R38, R39, R40: 47k; R_0402_1005Metric; MPN RC0402FR-0747KL
U1: SN74AXC8T245PWR; TSSOP-24_4.4x7.8mm_P0.65mm; MPN SN74AXC8T245PWR

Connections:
+3V3_GIGA: C1.1, U1.1 (VCCA), U1.2 (DIR1 HIGH); also elsewhere on the board
+3V3_PANEL: C2.1, U1.23 (VCCB), U1.24 (VCCB); also elsewhere on the board
BUF_R0: R1.1, U1.21 (B1)
BUF_R1: R2.1, U1.20 (B2)
BUF_R2: R3.1, U1.19 (B3)
BUF_R3: R4.1, U1.18 (B4)
BUF_R4: R5.1, U1.17 (B5)
BUF_R5: R6.1, U1.16 (B6)
BUF_R6: R7.1, U1.15 (B7)
BUF_R7: R8.1, U1.14 (B8)
GND: C1.2, C2.2, R33.2, R34.2, R35.2, R36.2, R37.2, R38.2, R39.2, R40.2, U1.11 (DIR2 LOW), U1.12 (GND), U1.13 (GND), U1.22 (~OE LOW); also elsewhere on the board
LCD_R0: R1.2; also elsewhere on the board
LCD_R1: R2.2; also elsewhere on the board
LCD_R2: R3.2; also elsewhere on the board
LCD_R3: R4.2; also elsewhere on the board
LCD_R4: R5.2; also elsewhere on the board
LCD_R5: R6.2; also elsewhere on the board
LCD_R6: R7.2; also elsewhere on the board
LCD_R7: R8.2; also elsewhere on the board
MCU_R0: R33.1, U1.3 (A1); also elsewhere on the board
MCU_R1: R34.1, U1.4 (A2); also elsewhere on the board
MCU_R2: R35.1, U1.5 (A3); also elsewhere on the board
MCU_R3: R36.1, U1.6 (A4); also elsewhere on the board
MCU_R4: R37.1, U1.7 (A5); also elsewhere on the board
MCU_R5: R38.1, U1.8 (A6); also elsewhere on the board
MCU_R6: R39.1, U1.9 (A7); also elsewhere on the board
MCU_R7: R40.1, U1.10 (A8); also elsewhere on the board

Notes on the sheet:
DIR1 = HIGH; DIR2 = LOW; OE = LOW. 33R series termination; 47k input bias. All channels A -> B.

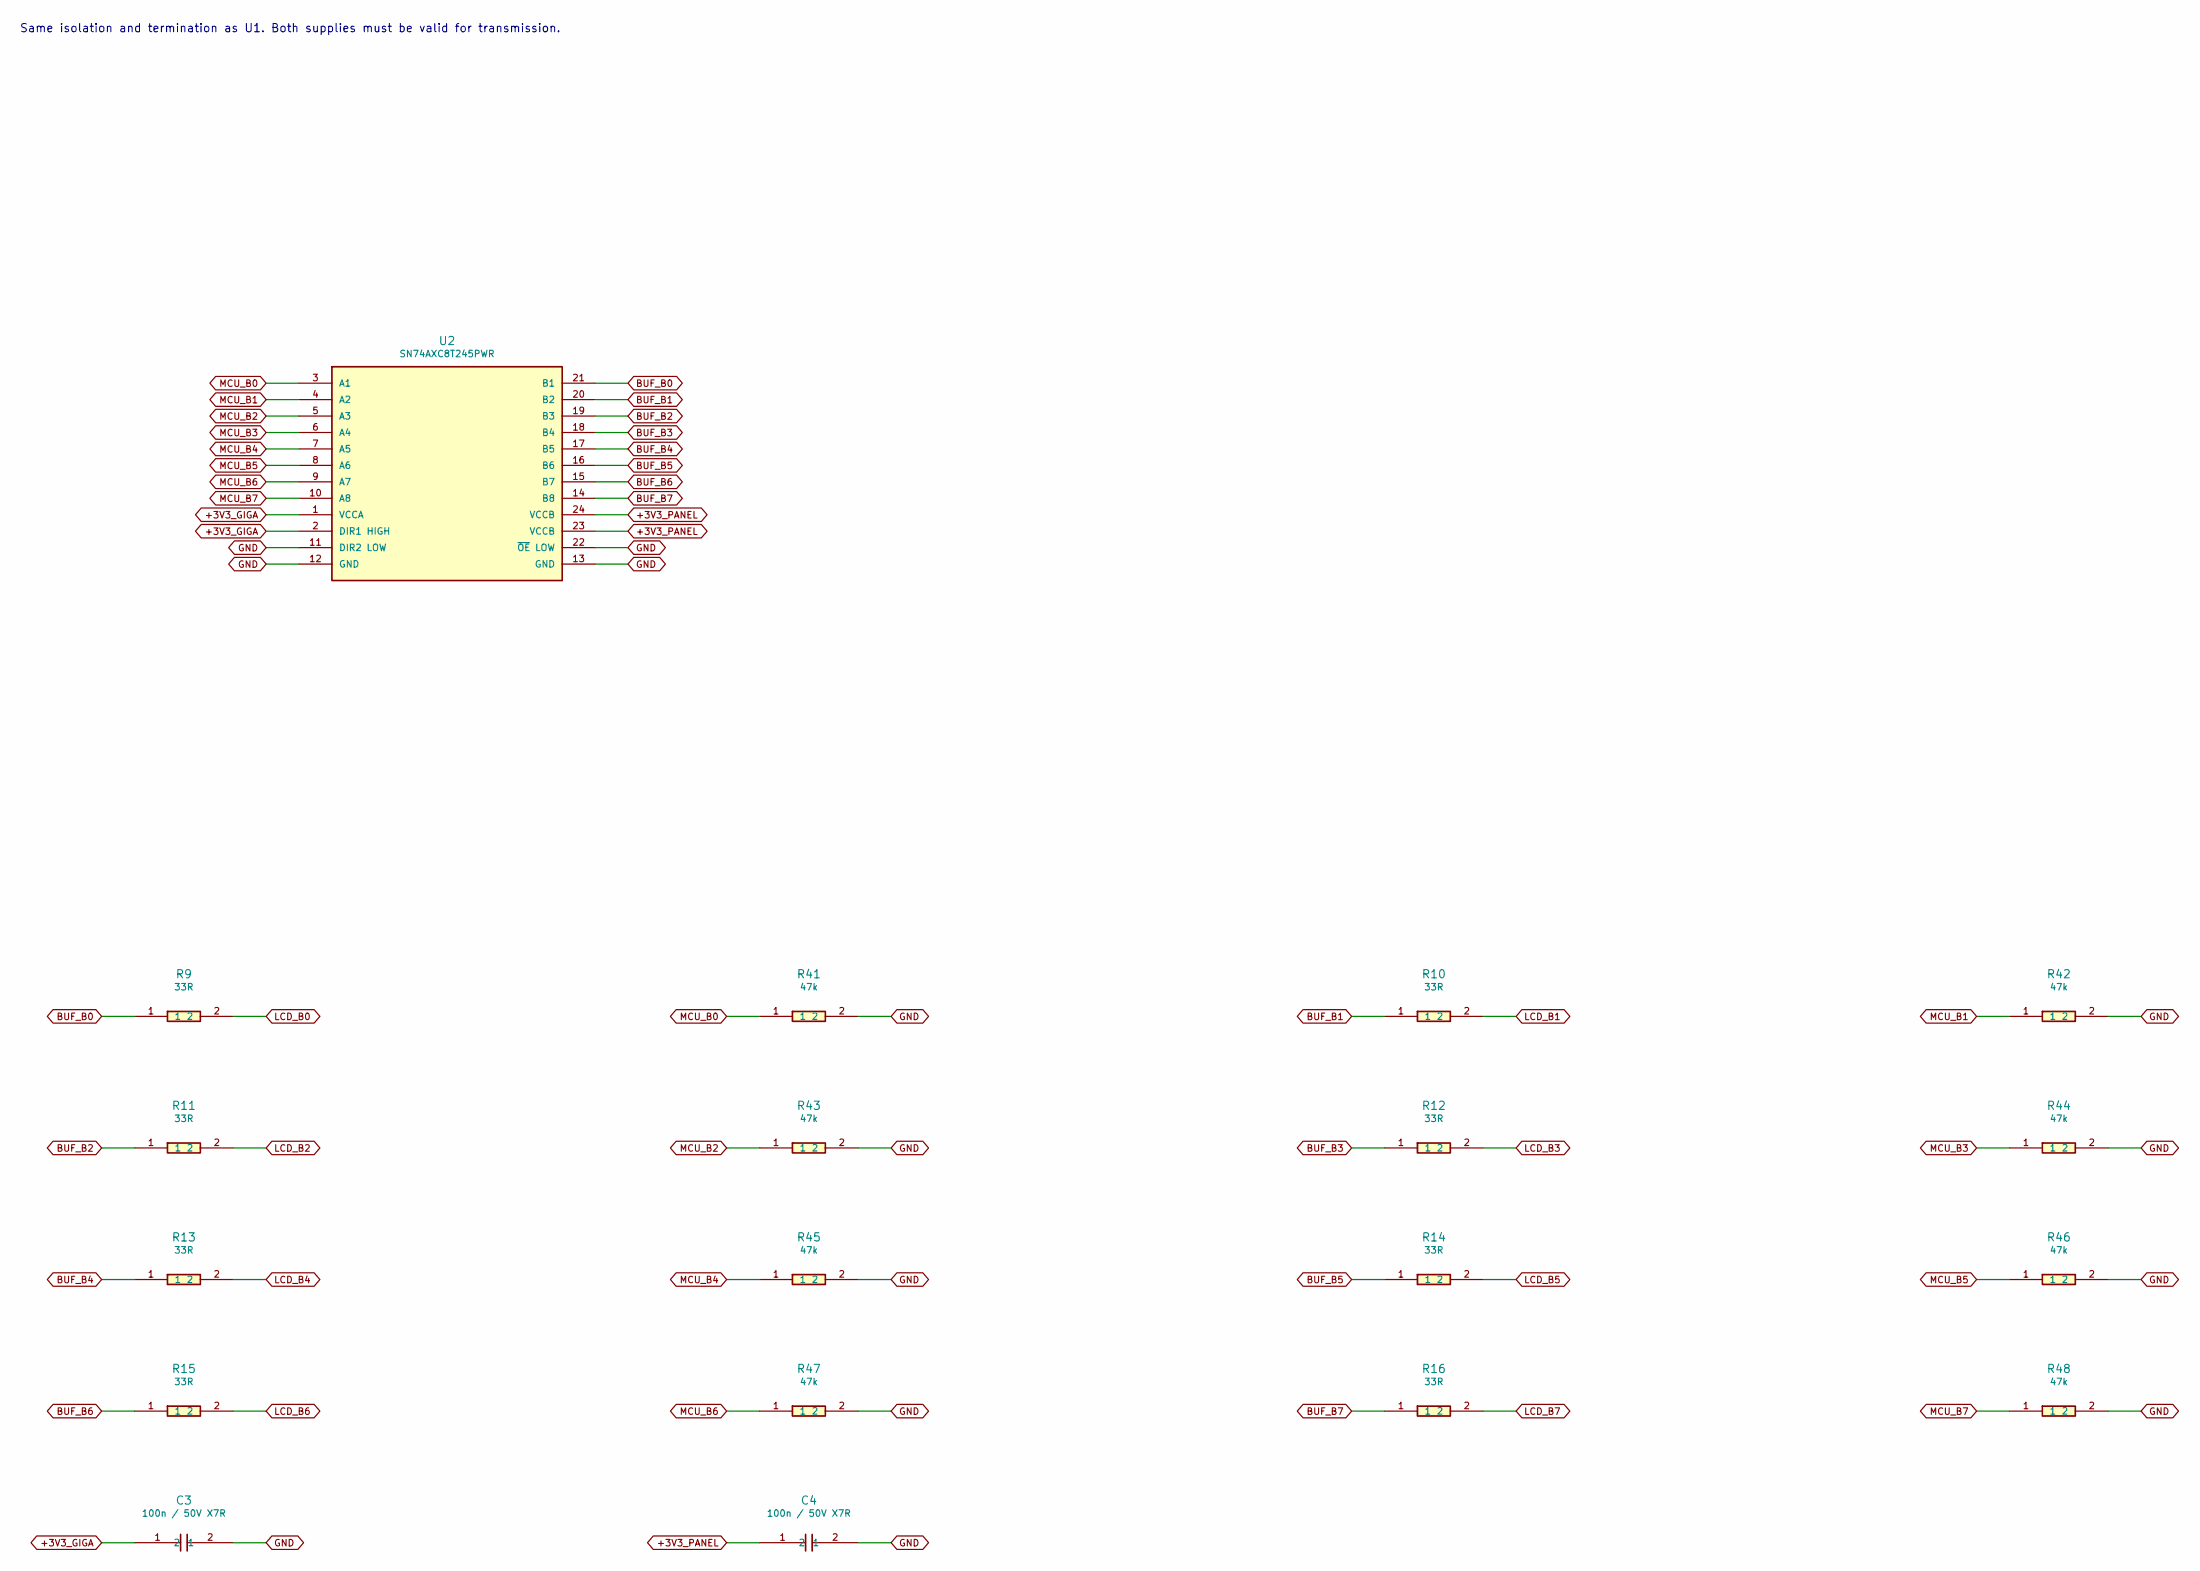
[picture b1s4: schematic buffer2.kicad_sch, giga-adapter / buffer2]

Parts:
C3, C4: 100n / 50V X7R; C_0603_1608Metric; MPN C0603C104K5RACTU
R9, R10, R11, R12, R13, R14, R15, R16: 33R; R_0402_1005Metric; MPN RC0402FR-0733RL
R41, R42, R43, R44, R45, R46, R47, R48: 47k; R_0402_1005Metric; MPN RC0402FR-0747KL
U2: SN74AXC8T245PWR; TSSOP-24_4.4x7.8mm_P0.65mm; MPN SN74AXC8T245PWR

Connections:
+3V3_GIGA: C3.1, U2.1 (VCCA), U2.2 (DIR1 HIGH); also elsewhere on the board
+3V3_PANEL: C4.1, U2.23 (VCCB), U2.24 (VCCB); also elsewhere on the board
BUF_B0: R9.1, U2.21 (B1)
BUF_B1: R10.1, U2.20 (B2)
BUF_B2: R11.1, U2.19 (B3)
BUF_B3: R12.1, U2.18 (B4)
BUF_B4: R13.1, U2.17 (B5)
BUF_B5: R14.1, U2.16 (B6)
BUF_B6: R15.1, U2.15 (B7)
BUF_B7: R16.1, U2.14 (B8)
GND: C3.2, C4.2, R41.2, R42.2, R43.2, R44.2, R45.2, R46.2, R47.2, R48.2, U2.11 (DIR2 LOW), U2.12 (GND), U2.13 (GND), U2.22 (~OE LOW); also elsewhere on the board
LCD_B0: R9.2; also elsewhere on the board
LCD_B1: R10.2; also elsewhere on the board
LCD_B2: R11.2; also elsewhere on the board
LCD_B3: R12.2; also elsewhere on the board
LCD_B4: R13.2; also elsewhere on the board
LCD_B5: R14.2; also elsewhere on the board
LCD_B6: R15.2; also elsewhere on the board
LCD_B7: R16.2; also elsewhere on the board
MCU_B0: R41.1, U2.3 (A1); also elsewhere on the board
MCU_B1: R42.1, U2.4 (A2); also elsewhere on the board
MCU_B2: R43.1, U2.5 (A3); also elsewhere on the board
MCU_B3: R44.1, U2.6 (A4); also elsewhere on the board
MCU_B4: R45.1, U2.7 (A5); also elsewhere on the board
MCU_B5: R46.1, U2.8 (A6); also elsewhere on the board
MCU_B6: R47.1, U2.9 (A7); also elsewhere on the board
MCU_B7: R48.1, U2.10 (A8); also elsewhere on the board

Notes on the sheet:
Same isolation and termination as U1. Both supplies must be valid for transmission.

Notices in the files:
README.md:
TGX's [LGPL-2.1 license](external/tgx/LICENSE) and upstream provenance remain in
